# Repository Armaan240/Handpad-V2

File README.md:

# Handpad-V2
polished version of first handpad !!

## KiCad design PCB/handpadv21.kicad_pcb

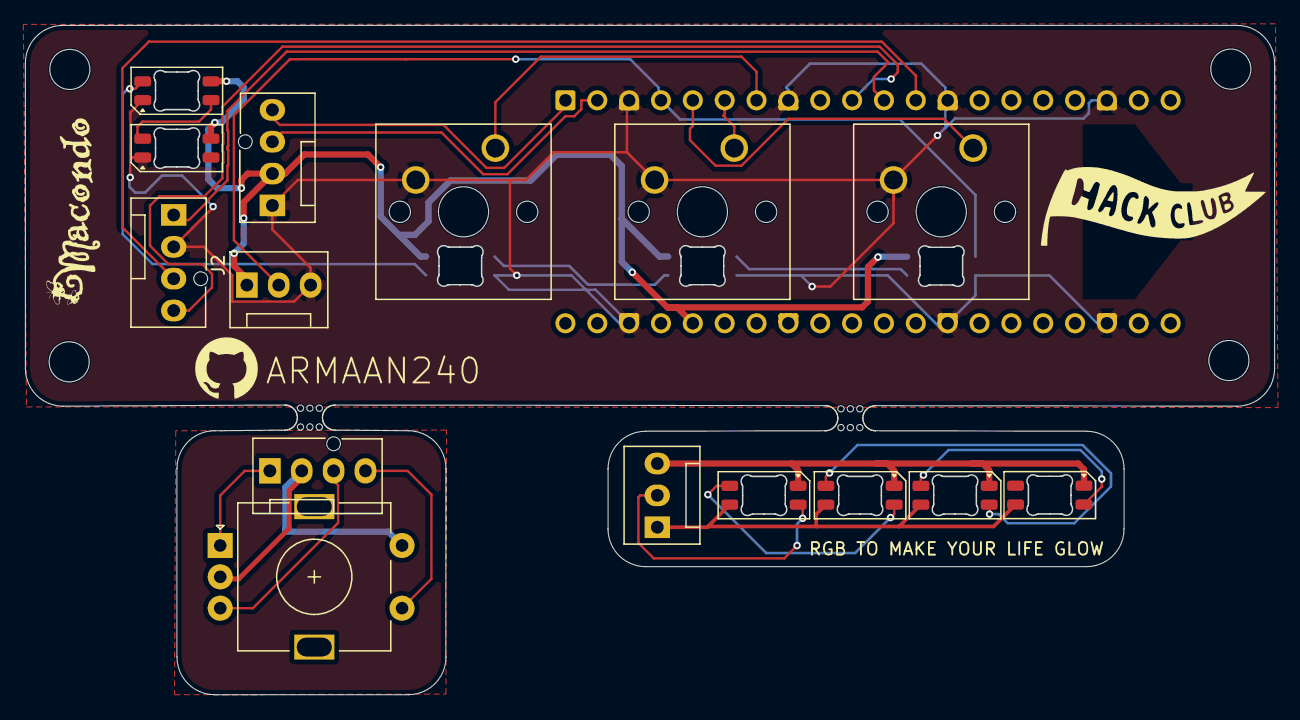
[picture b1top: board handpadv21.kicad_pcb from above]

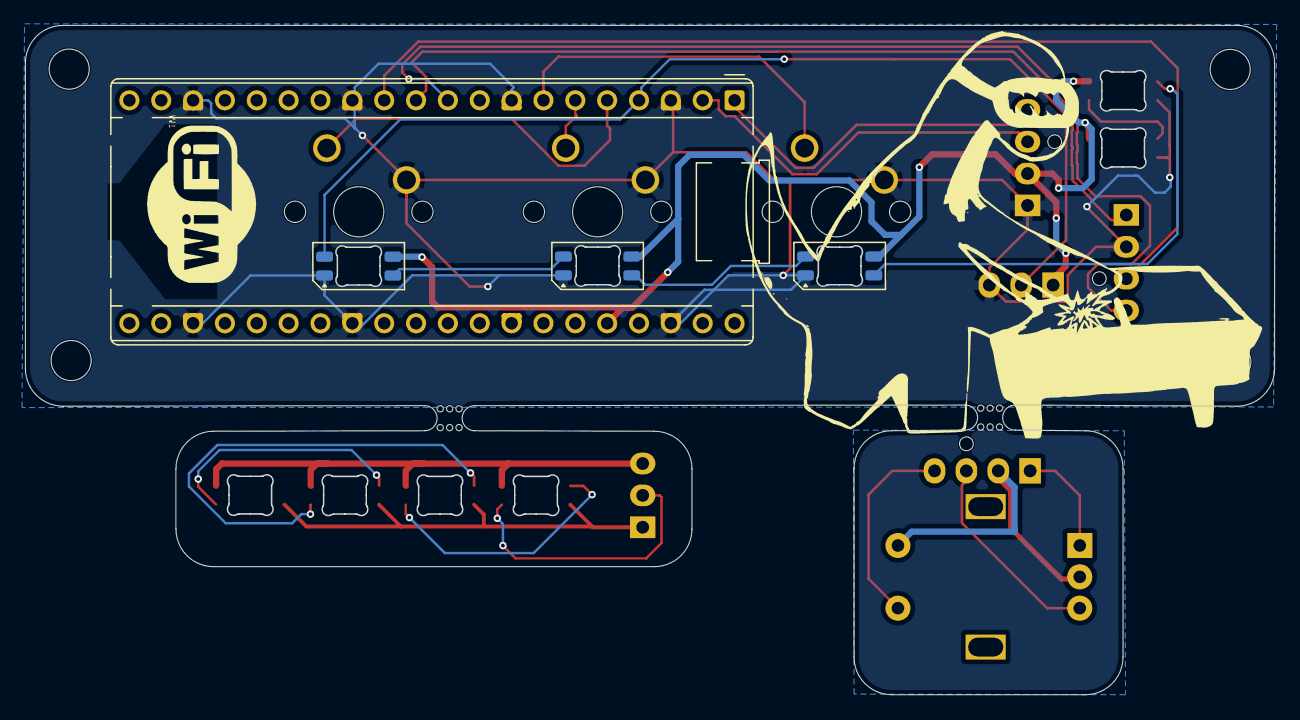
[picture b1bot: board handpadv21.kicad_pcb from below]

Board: 2 copper layers, 99.5 x 53.3 mm, 25 parts (4 on the bottom side), 25 nets.

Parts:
A1: RaspberryPi_Pico_W; RaspberryPi_Pico_Common_THT
D1, D2, D3, D4, D5, D7, D8, D9, D10: SK6812MINI-E; LED_SK6812MINI-E_3.2x2.8mm_P1.5mm_ReverseMount
H1, H2, H3, H4: MountingHole; MountingHole_3.2mm_M3
J1, J4: Conn_01x03_Socket; FanPinHeader_1x03_P2.54mm_Vertical
J2, J3: Conn_01x04_Socket; FanPinHeader_1x04_P2.54mm_Vertical
SW1, SW2, SW3: SW_Push; SW_Cherry_MX_1.00u_PCB
SW5: RotaryEncoder_Switch; RotaryEncoder_Alps_EC11E-Switch_Vertical_H20mm
U1: OLEDM0.91; FanPinHeader_1x04_P2.54mm_Vertical
mouse-bite-2mm-slot, mouse-bite-2mm-slot#2: VAL**; mouse-bite-2mm-slot

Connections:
+3.3V: A1.36 (3V3), D1.3 (VDD), D2.3 (VDD), D3.3 (VDD), D4.3 (VDD), D5.3 (VDD), J4.1, U1.2 (VCC)
/DIN: A1.4 (GPIO2), D1.2 (DIN), J4.2
/E1: A1.11 (GPIO8), J2.1
/E2: A1.12 (GPIO9), J2.3
/S1: A1.5 (GPIO3), SW1.1
/S2: A1.6 (GPIO4), SW2.1
/S3: A1.7 (GPIO5), SW3.1
/S5: A1.10 (GPIO7), J2.4
/SCl: A1.2 (GPIO1), U1.3 (SCL)
/SDA: A1.1 (GPIO0), U1.4 (SDA)
GND: A1.3 (GND), A1.8 (GND), A1.13 (GND), A1.18 (GND), A1.23 (GND), A1.28 (GND), A1.38 (GND), D1.1 (VSS), D2.1 (VSS), D3.1 (VSS), D4.1 (VSS), D5.1 (VSS), J2.2, J4.3, SW1.2, SW2.2, SW3.2, U1.1 (GND)
unnamed: D1.4 (DOUT), D2.2 (DIN)
unnamed: D2.4 (DOUT), D3.2 (DIN)
unnamed: D3.4 (DOUT), D4.2 (DIN)
unnamed: D4.4 (DOUT), D5.2 (DIN)
unnamed: D7.2 (DIN), J1.2
unnamed: D7.4 (DOUT), D8.2 (DIN)
unnamed: D8.4 (DOUT), D9.2 (DIN)
unnamed: D9.4 (DOUT), D10.2 (DIN)
unnamed: D7.3 (VDD), D8.3 (VDD), D9.3 (VDD), D10.3 (VDD), J1.1
unnamed: D7.1 (VSS), D8.1 (VSS), D9.1 (VSS), D10.1 (VSS), J1.3
unnamed: J3.1, SW5.A
unnamed: J3.2, SW5.C, SW5.S2
unnamed: J3.3, SW5.B
unnamed: J3.4, SW5.S1

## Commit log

2026-06-22 Add initial README for PCB folder
2026-06-22 Add initial README for handpad project
2026-06-22 Add readme.md for CAD files description
2026-06-22 Update README with additional screenshots
    Added multiple screenshots to showcase the polished version.
